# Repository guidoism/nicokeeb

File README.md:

# nicokeeb

He wants to ease himself into weird keyboards. 
He said he like the ortholinear rather than column stagger for now. 
So maybe make a 14x5 ortho with an inverted t cursor section.

    points:
      mirror:
        ref: ortho_inner_home
        distance: 1U
      zones:
        ortho:
          columns:
            farfarpinky:
            farpinky:
            pinky:
            ring:
            middle:
            index:
            inner:
          rows:
            mods:
            bottom:
            home:
            top:
            nums:

    [{a:7},"`","1","2","3","4","5","6","7","8","9","0","-","+","DEL",{x:0.25},"","",""],
    ["Tab","Q","W","E","R","T","Y","U","I","O","P","[","]","\\",{x:0.25},"","",""],
    ["Ctrl","A","S","D","F","G","H","J","K","L",";","'","","",{x:0.25},"","",""],
    ["Shift","Z","X","C","V","B","N","M",",",".","/","Shift","","",{x:1.25},"&uarr;"],
    ["","Ctrl","Alt","Super","&dArr;",{w:2},"","","","","","","","",{x:0.25},"&larr;","&darr;","&rarr;"]

Now with full 5x5 parts

    [{a:7},"`","1","2","3","4","5","6","7","8","9","0","-","+","DEL","",{x:1},"","",""],
    ["Tab","Q","W","E","R","T","Y","U","I","O","P","[","]","\\","",{x:1},"","",""],
    ["Caps","A","S","D","F","G","H","J","K","L",";","'","","","",{x:1},"","",""],
    ["Shift","Z","X","C","V","B","N","M",",",".","/","Shift","","","",{x:2},"&uarr;"],
    ["Ctrl","Win","Alt","Super","",{w:2},"","","","","","","","","",{x:1},"&larr;","&darr;","&rarr;"]

Using three 5x5 parts we will get a 15x5 ortho which will use 15+5=20 pins unoptimized.

If we used four 5x5 parts we will need 20+5=25 pins. The Pico has 26 gpio so that should work.

If we could optimize it to be a 2x2 grid of the 5x5 parts then it would only need 10+10=20 pins.

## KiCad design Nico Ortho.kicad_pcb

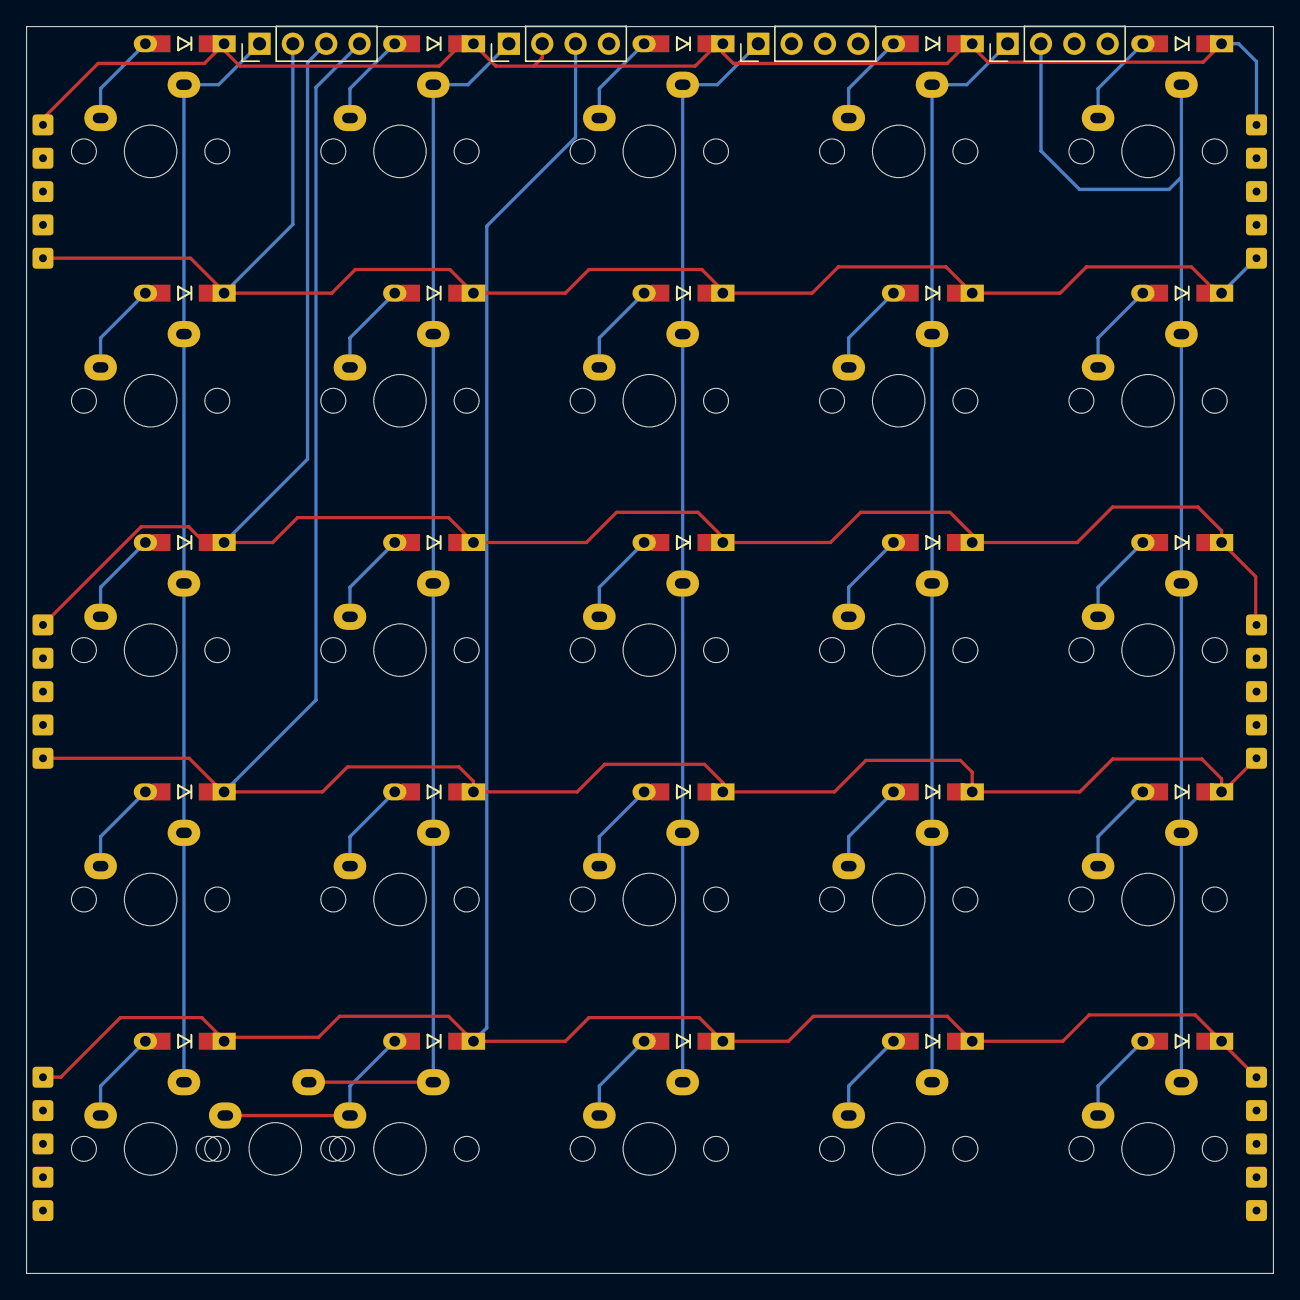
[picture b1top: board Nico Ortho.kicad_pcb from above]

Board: 2 copper layers, 95.0 x 95.0 mm, 81 parts (0 on the bottom side), 10 nets.

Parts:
D33, D34, D35, D36, D37, D38, D39, D40, D41, D42, D43, D44, D45, D46, D47, D48, D49, D50, D51, D52, D53, D54, D55, D56, D57: D; D3_TH_SMD_v2
REFr, REFr1, REFr2, REFr3, REFr4, REFr5, REFr5#2, REFr5#3, REFr6, REFr6#2, REFr6#3, REFr7, REFr7#2, REFr7#3, REFr8, REFr8#2, REFr8#3, REFr9, REFr9#2, REFr9#3, REFr10, REFr10#2, REFr11, REFr11#2, REFr12, REFr12#2, REFr13, REFr13#2, REFr14, REFr14#2: SolderWire-0.1sqmm_1x01_D0.4mm_OD1mm
SW6, SW6#2, SW7, SW8, SW9, SW10, SW11, SW12, SW13, SW14, SW15, SW16, SW17, SW18, SW19, SW20, SW21, SW22, SW23, SW24, SW25, SW26, SW27, SW28, SW29, SW30: SW_PUSH; CherryMX_1u

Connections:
col1: SW6#2.2, SW11.2, SW16.2, SW21.2, SW26.2
col2: SW6.2, SW7.2, SW12.2, SW17.2, SW22.2, SW27.2
col3: SW8.2, SW13.2, SW18.2, SW23.2, SW28.2
col4: SW9.2, SW14.2, SW19.2, SW24.2, SW29.2
col5: SW10.2, SW15.2, SW20.2, SW25.2, SW30.2
row1: D33.1, D34.1, D35.1, D36.1, D37.1, REFr.1, REFr5#3.1
row2: D38.1, D39.1, D40.1, D41.1, D42.1, REFr4.1, REFr9.1
row3: D43.1, D44.1, D45.1, D46.1, D47.1, REFr5.1, REFr10.1
row4: D48.1, D49.1, D50.1, D51.1, D52.1, REFr9#3.1, REFr14#2.1
row5: D53.1, D54.1, D55.1, D56.1, D57.1, REFr5#2.1, REFr10#2.1

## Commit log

2023-06-01 Checkpoint
